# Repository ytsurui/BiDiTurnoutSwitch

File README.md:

# BiDi Turnout Switch

NMRA DCC 規格のうち、BiDi (RailCom) によって送信される車両のアドレス情報を利用して、接続されているポイント線路を自動的に転換することが可能な装置です。

本リポジトリには、基板設計データとファームウェアが含まれます。

## 開発環境

- KiCad Version (5.1.12)-1
- Microchip Studio Version 7.0.2542

## 各種ドキュメント

  * [パーツリスト](docs/partslist.md)

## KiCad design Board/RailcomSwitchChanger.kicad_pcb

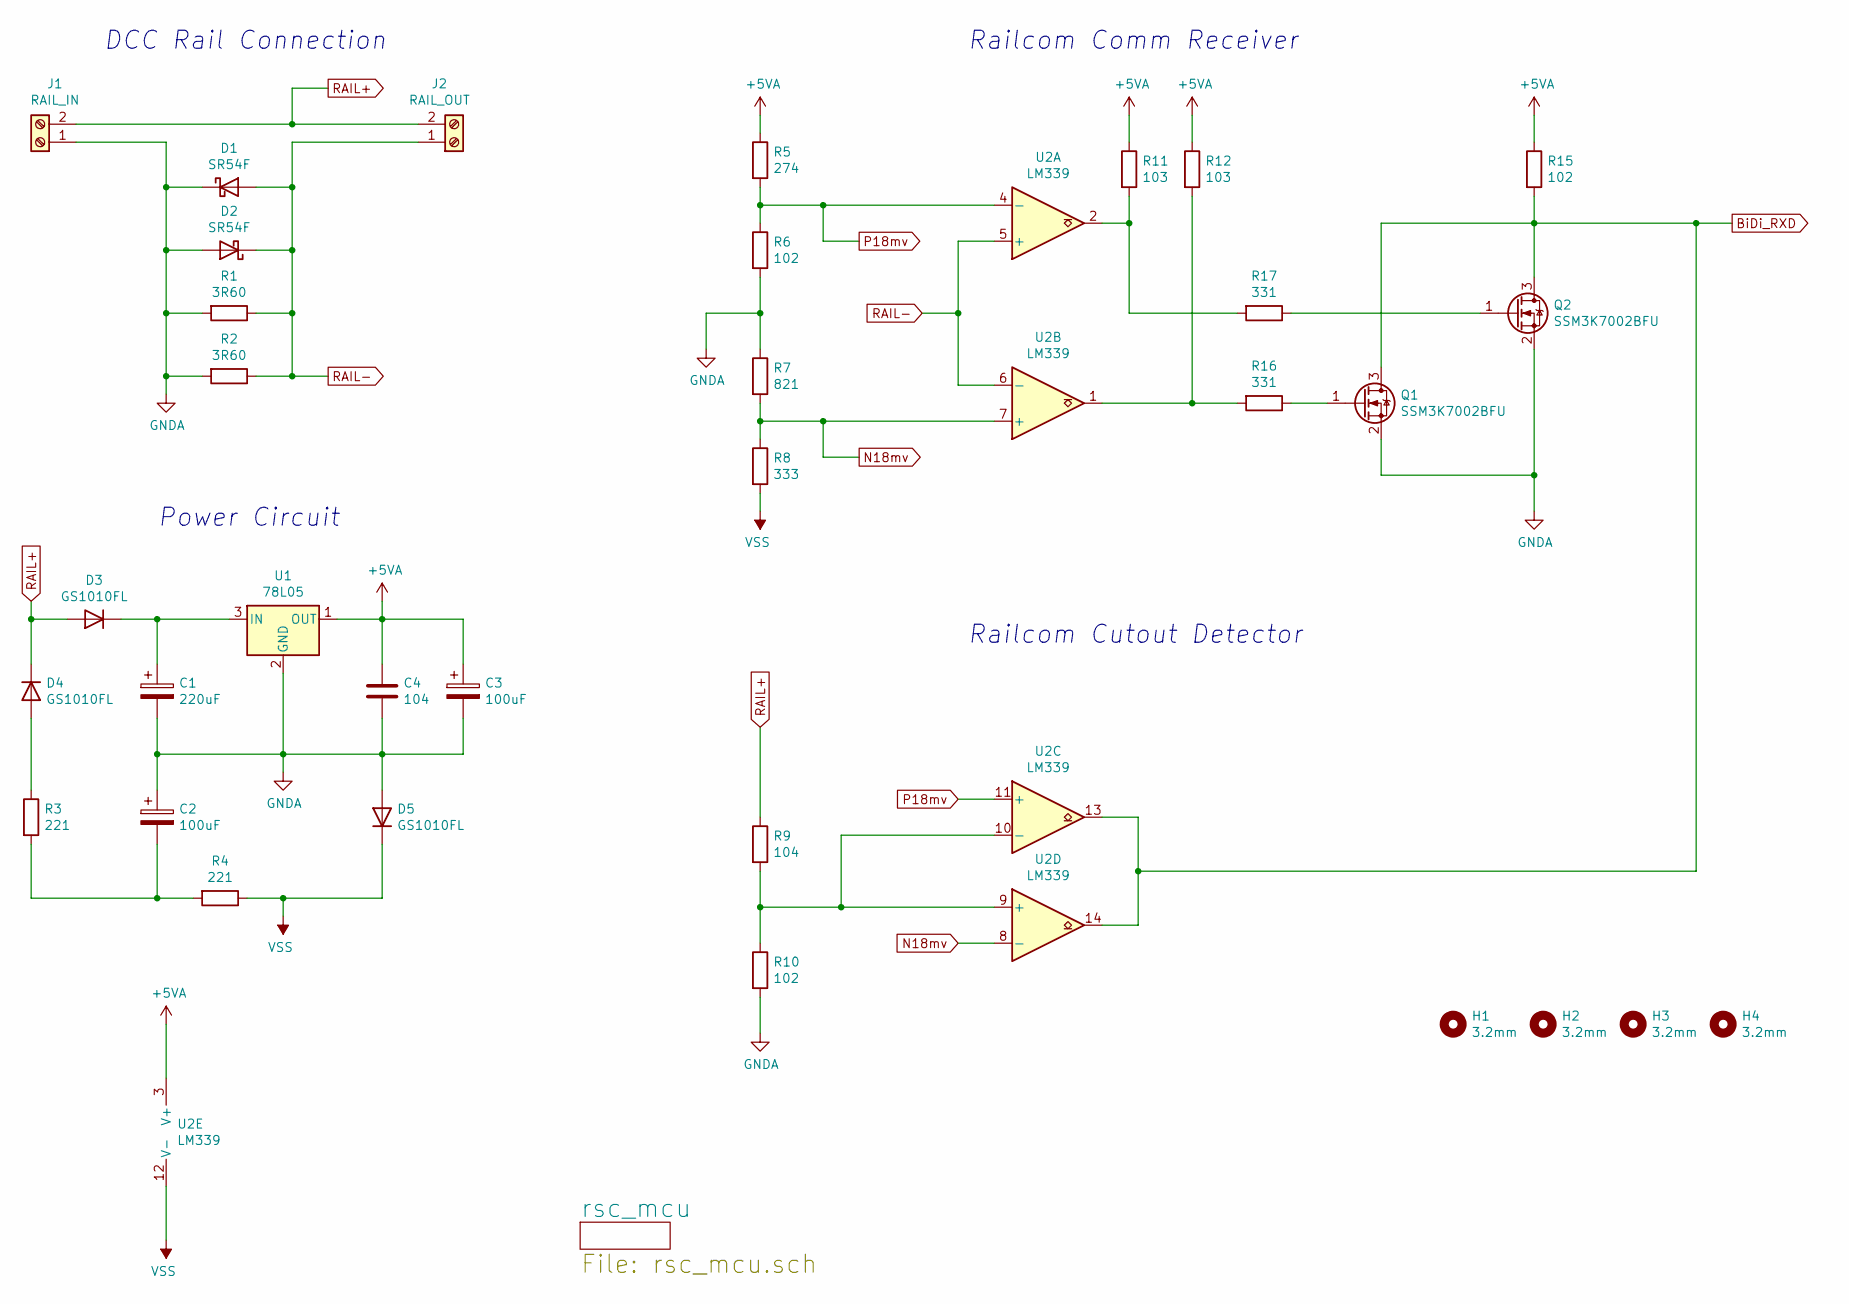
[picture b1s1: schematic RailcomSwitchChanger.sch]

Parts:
C1: 220uF; CAP_TH_6.3x11
C2, C3: 100uF; CAP_TH_5x11
C4: 104; C_1005
D1, D2: SR54F; SMBF
D3, D4, D5: GS1010FL; SOD-123FL
H1, H2, H3, H4: 3.2mm; HOLE_3.2mm
J1: RAIL_IN; TB111-2
J2: RAIL_OUT; TB111-2
Q1, Q2: SSM3K7002BFU; SC-70
R1, R2: 3R60; R_3225
R3, R4: 221; R_1608
R5: 274; R_1608
R6, R10, R15: 102; R_1608
R7: 821; R_1608
R8: 333; R_1608
R9: 104; R_1608
R11, R12: 103; R_1608
R16, R17: 331; R_1608
U1: 78L05; SOT-89-3
U2: LM339; SOIC-14

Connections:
+5VA: C3.1, C4.1, R5.1, R11.1, R12.1, R15.1, U1.1 (OUT), U2.3 (V+)
BiDi_RXD: Q1.3 (D), Q2.3 (D), R15.2, U2.13, U2.14; also elsewhere on the board
GNDA: C1.2, C2.1, C3.2, C4.2, D1.1 (K), D2.2 (A), D5.2 (A), J1.1, Q1.2 (S), Q2.2 (S), R1.2, R2.2, R6.2, R7.1, R10.2, U1.2 (GND); also elsewhere on the board
N18mv: R7.2, R8.1, U2.7 (+), U2.8 (-)
unnamed: C1.1, D3.1 (K), U1.3 (IN)
unnamed: C2.2, R3.2, R4.2
unnamed: D4.2 (A), R3.1
unnamed: Q1.1 (G), R16.1
unnamed: Q2.1 (G), R17.1
unnamed: R9.2, R10.1, U2.9 (+), U2.10 (-)
unnamed: R11.2, R17.2, U2.2
unnamed: R12.2, R16.2, U2.1
P18mv: R5.2, R6.1, U2.4 (-), U2.11 (+)
RAIL+: D3.2 (A), D4.1 (K), J1.2, J2.2, R9.1; also elsewhere on the board
RAIL-: D1.2 (A), D2.1 (K), J2.1, R1.1, R2.1, U2.5 (+), U2.6 (-)
VSS: D5.1 (K), R4.1, R8.2, U2.12 (V-)

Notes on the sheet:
Railcom Cutout Detector
Power Circuit
DCC Rail Connection
Railcom Comm Receiver

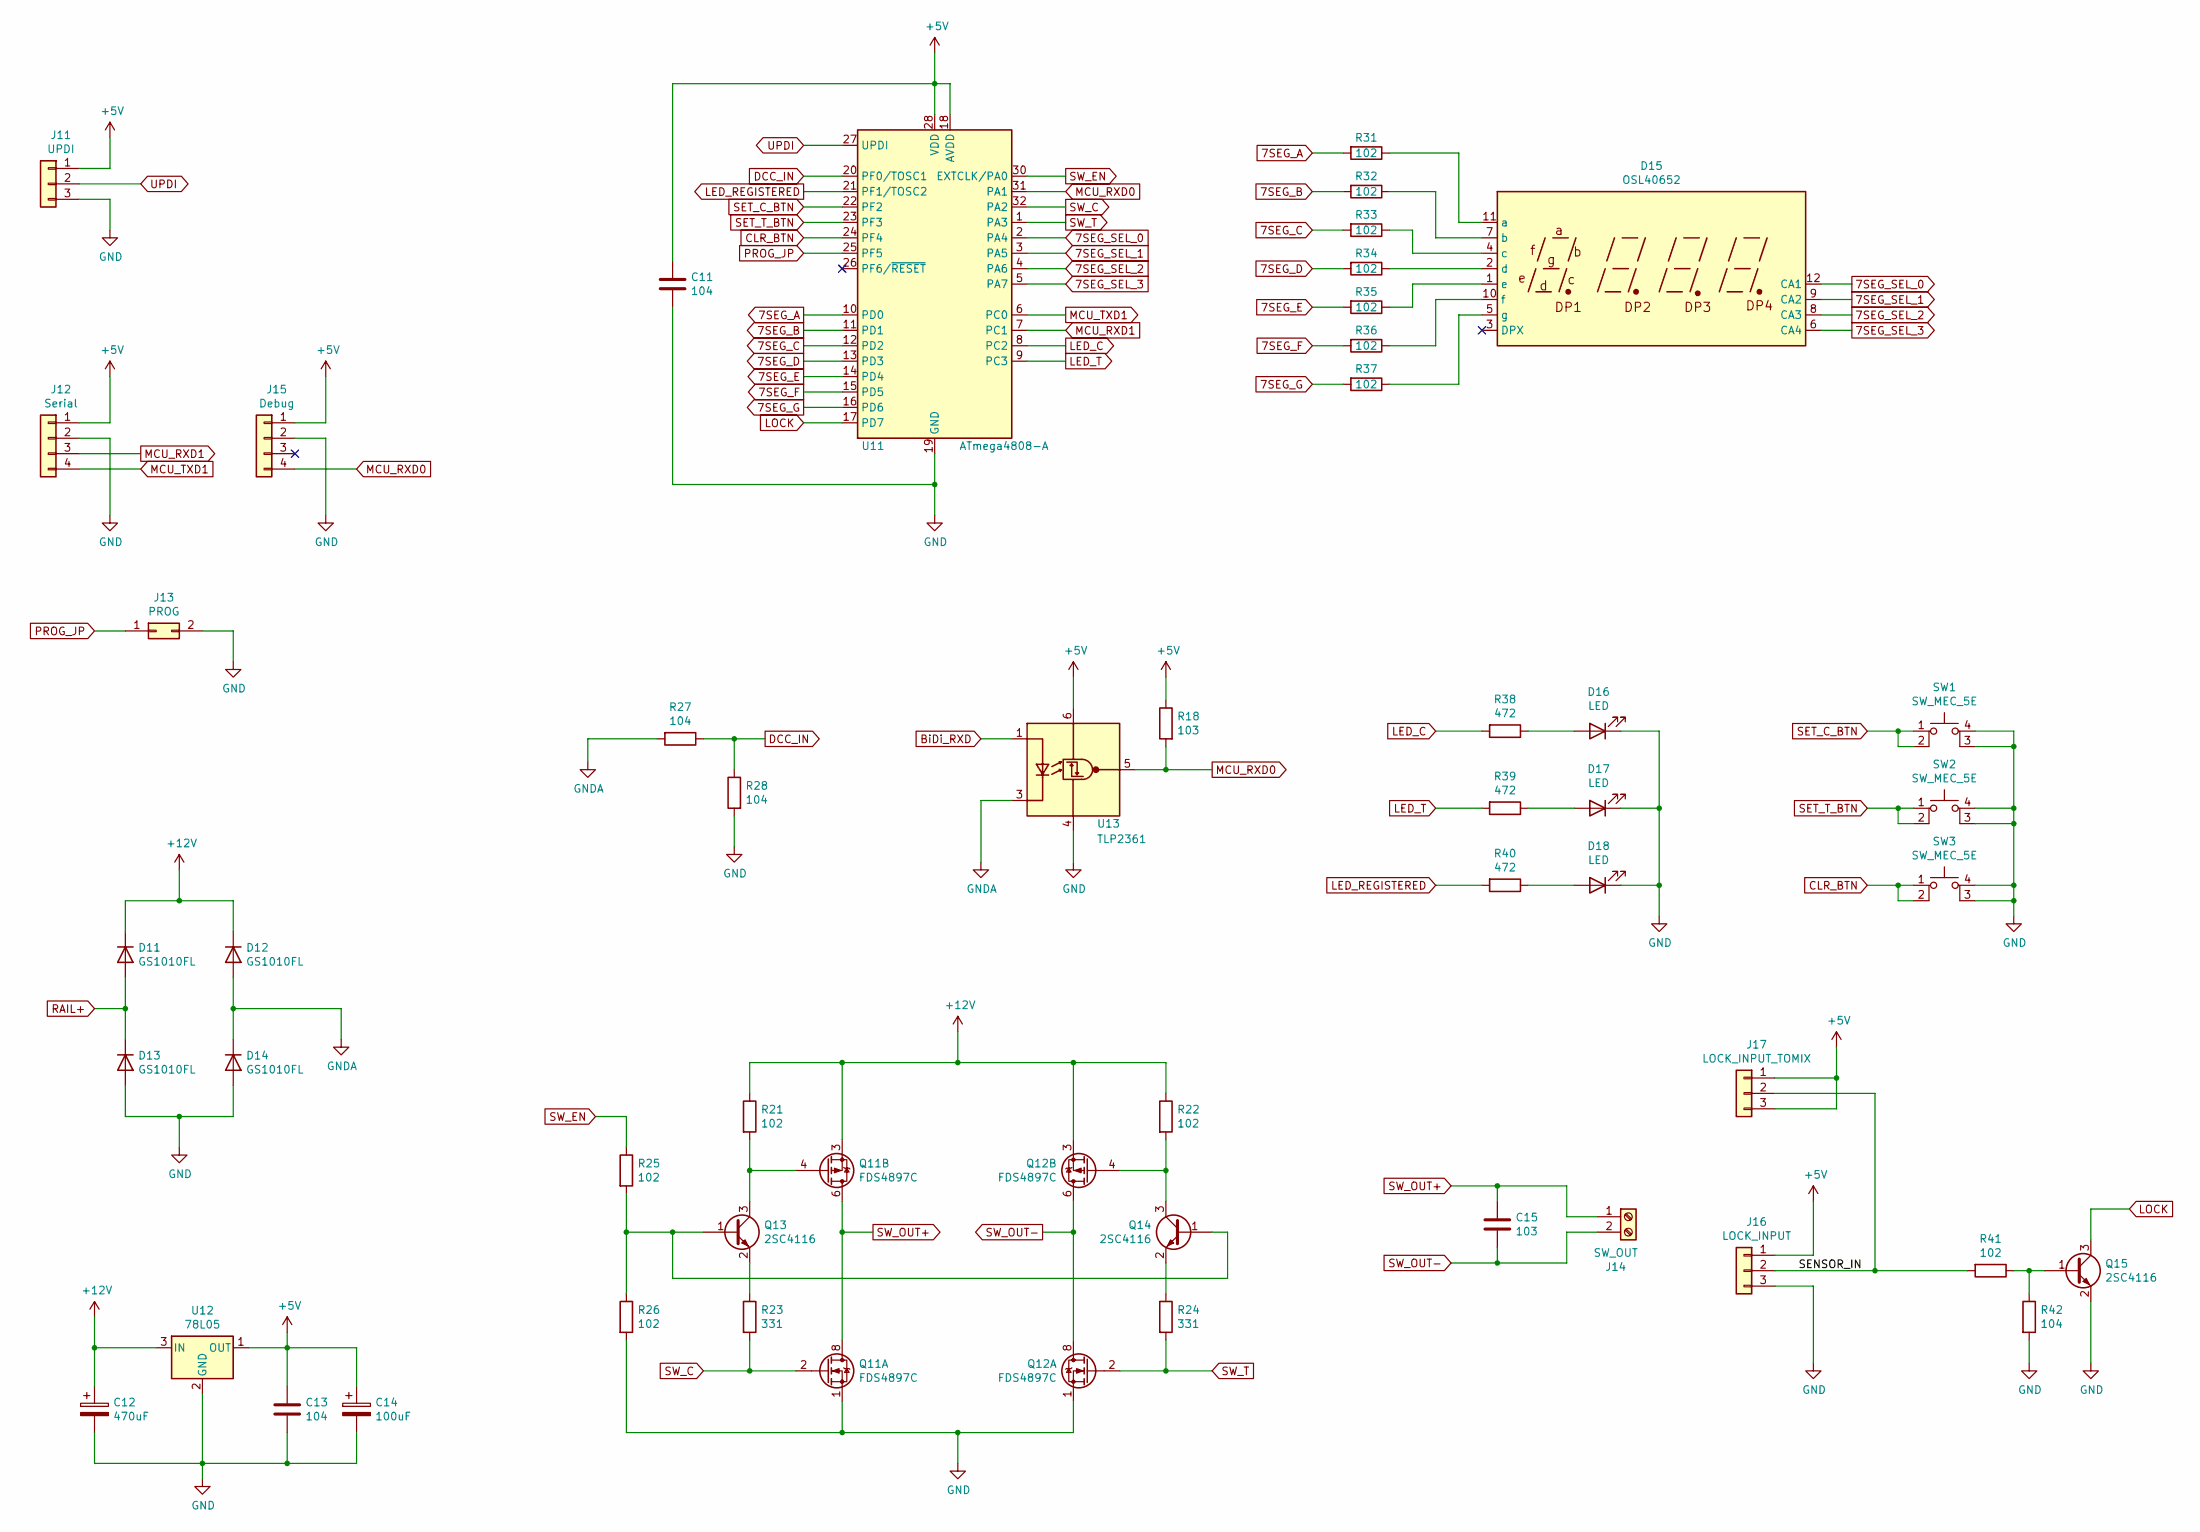
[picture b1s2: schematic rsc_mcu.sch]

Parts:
C11, C13: 104; C_1005
C12: 470uF; CAP_TH_8x11_5
C14: 100uF; CAP_TH_5x11
C15: 103; C_1005
D11, D12, D13, D14: GS1010FL; SOD-123FL
D15: OSL40652; OSL40562
D16, D17, D18: LED; LED_1608
J11: UPDI; PinHeader_01x03
J12: Serial; pin_array_1x4
J13: PROG; pin_array_1x2
J14: SW_OUT; TB111-2
J15: Debug; pin_array_1x4
J16: LOCK_INPUT; PinHeader_01x03
J17: LOCK_INPUT_TOMIX; Molex_0530480350
Q11, Q12: FDS4897C; SO-8
Q13, Q14, Q15: 2SC4116; SC-70
R18: 103; R_1608
R21, R22, R25, R26, R31, R32, R33, R34, R35, R36, R37, R41: 102; R_1608
R23, R24: 331; R_1608
R27, R28, R42: 104; R_1608
R38, R39, R40: 472; R_1608
SW1, SW2, SW3: SW_MEC_5E; TS-0606
U11: ATmega4808-A; TQFP-32_7x7mm_P0.8mm
U12: 78L05; SOT-89-3
U13: TLP2361; SO-6_5pin

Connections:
7SEG_A: R31.2, U11.10 (PD0)
7SEG_B: R32.2, U11.11 (PD1)
7SEG_C: R33.2, U11.12 (PD2)
7SEG_D: R34.2, U11.13 (PD3)
7SEG_E: R35.2, U11.14 (PD4)
7SEG_F: R36.2, U11.15 (PD5)
7SEG_G: R37.2, U11.16 (PD6)
7SEG_SEL_0: D15.12 (CA1), U11.2 (PA4)
7SEG_SEL_1: D15.9 (CA2), U11.3 (PA5)
7SEG_SEL_2: D15.8 (CA3), U11.4 (PA6)
7SEG_SEL_3: D15.6 (CA4), U11.5 (PA7)
+5V: C11.1, C13.1, C14.1, J11.1, J12.1, J15.1, J16.1, J17.1, J17.3, R18.1, U11.18 (AVDD), U11.28 (VDD), U12.1 (OUT), U13.6 (VDD)
+12V: C12.1, D11.1 (K), D12.1 (K), Q11.3 (1), Q12.3 (1), R21.1, R22.1, U12.3 (IN)
/rsc_mcu/SENSOR_IN: J16.2, J17.2, R41.2
BiDi_RXD: U13.1 (A); also elsewhere on the board
CLR_BTN: SW3.1, SW3.2, U11.24 (PF4)
DCC_IN: R27.1, R28.1, U11.20 (PF0/TOSC1)
GND: C11.2, C12.2, C13.2, C14.2, D13.2 (A), D14.2 (A), D16.1 (K), D17.1 (K), D18.1 (K), J11.3, J12.2, J13.2, J15.2, J16.3, Q11.1 (S), Q12.1 (S), Q15.2 (E), R26.2, R28.2, R42.2, SW1.3 (K), SW1.4 (A), SW2.3 (K), SW2.4 (A), SW3.3 (K), SW3.4 (A), U11.19 (GND), U11.29 (GND), U12.2 (GND), U13.4 (GND)
GNDA: D12.2 (A), D14.1 (K), R27.2, U13.3 (K); also elsewhere on the board
LED_C: R38.2, U11.8 (PC2)
LED_REGISTERED: R40.2, U11.21 (PF1/TOSC2)
LED_T: R39.2, U11.9 (PC3)
LOCK: Q15.3 (C), U11.17 (PD7)
MCU_RXD0: J15.4, R18.2, U11.31 (PA1), U13.5 (VO)
MCU_RXD1: J12.3, U11.7 (PC1)
MCU_TXD1: J12.4, U11.6 (PC0)
unnamed: D15.1 (e), R35.1
unnamed: D15.2 (d), R34.1
unnamed: D15.4 (c), R33.1
unnamed: D15.5 (g), R37.1
unnamed: D15.7 (b), R32.1
unnamed: D15.10 (f), R36.1
unnamed: D15.11 (a), R31.1
unnamed: D16.2 (A), R38.1
unnamed: D17.2 (A), R39.1
unnamed: D18.2 (A), R40.1
unnamed: Q11.4 (G), Q13.3 (C), R21.2
unnamed: Q12.4 (G), Q14.3 (C), R22.2
unnamed: Q13.1 (B), Q14.1 (B), R25.2, R26.1
unnamed: Q13.2 (E), R23.1
unnamed: Q14.2 (E), R24.1
unnamed: Q15.1 (B), R41.1, R42.1
PROG_JP: J13.1, U11.25 (PF5)
RAIL+: D11.2 (A), D13.1 (K); also elsewhere on the board
SET_C_BTN: SW1.1, SW1.2, U11.22 (PF2)
SET_T_BTN: SW2.1, SW2.2, U11.23 (PF3)
SW_C: Q11.2 (G), R23.2, U11.32 (PA2)
SW_EN: R25.1, U11.30 (EXTCLK/PA0)
SW_OUT+: C15.1, J14.1, Q11.5 (D), Q11.6 (D), Q11.7 (D), Q11.8 (D)
SW_OUT-: C15.2, J14.2, Q12.5 (D), Q12.6 (D), Q12.7 (D), Q12.8 (D)
SW_T: Q12.2 (G), R24.2, U11.1 (PA3)
UPDI: J11.2, U11.27 (UPDI)

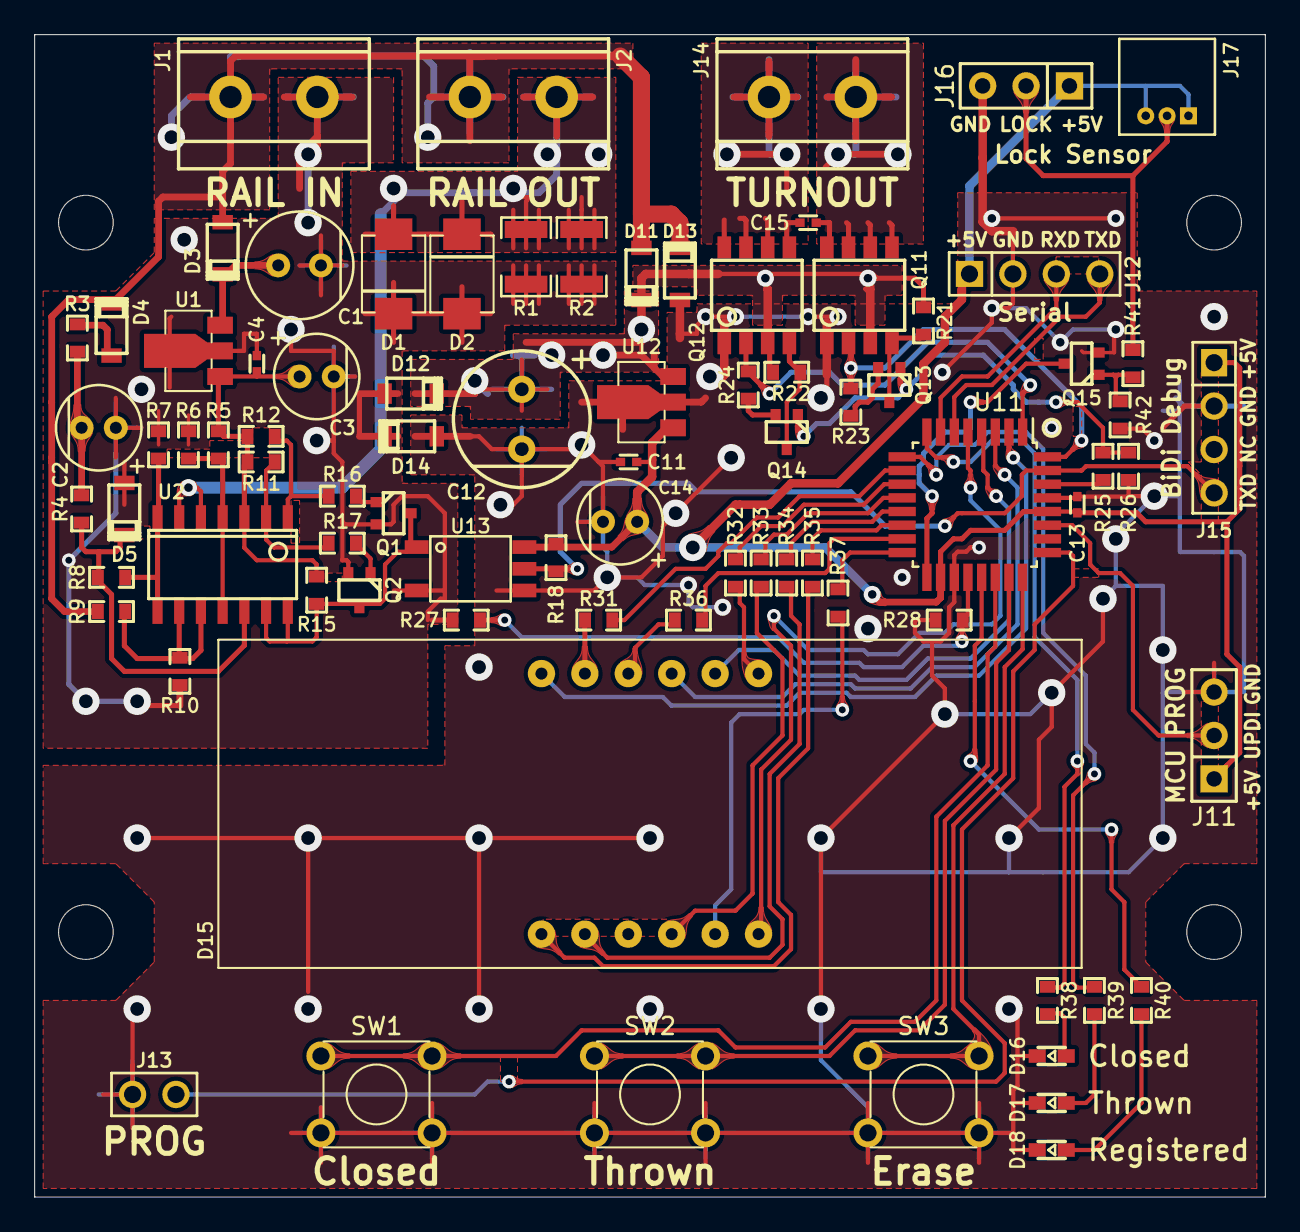
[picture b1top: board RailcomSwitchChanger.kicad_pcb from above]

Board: 2 copper layers, 72.0 x 68.0 mm, 86 parts (0 on the bottom side), 65 nets.

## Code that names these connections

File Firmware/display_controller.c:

/*
 * display_controller.c
 *
 * Created: 2021/12/31 0:49:56
 *  Author: Y.Tsurui
 */ 

#include <avr/io.h>
#include <avr/interrupt.h>
#include <avr/pgmspace.h>

#include "display_controller.h"

#define LED_A 0x01
#define LED_B 0x02
#define LED_C 0x04
#define LED_D 0x08
#define LED_E 0x10
#define LED_F 0x20
#define LED_G 0x40

uint8_t data_cache[4];
uint8_t select_flag = 0;

uint8_t power_flag = 0;

uint8_t appTimerFlag = 0;

//7-seg LED Port Assign
/*
A: PD0
B: PD1
C: PD2
D: PD3
E: PD4
F: PD5
G: PD6

CA1: PA4
CA2: PA5
CA3: PA6
CA4: PA7
*/

void set_port(uint8_t dec);

/*
ISR(TIMER1_COMPA_vect)
{
	appTimerFlag = 1;
	
	PORTD &= 0b11000011;
	
	if (power_flag) {
		PORTB &= 0x80;
		return;
	} else {
		set_port(data_cache[select_flag]);
		select_flag++;
	}	
	
	if (select_flag == 1) {
		PORTD |= 0b00000100;
	} else if (select_flag == 2) {
		PORTD |= 0b00010000;
	} else if (select_flag == 3) {
		PORTD |= 0b00100000;
	} else {
		PORTD |= 0b00001000;
		select_flag = 0;
	}
}

void set_7seg_timer(void)
{
	TCCR1A = 0b00000000;
	TCCR1B = 0b00001011;
	OCR1A = 128;
	OCR1B = OCR1A / 2;
	
	TIMSK |= 0b01000000;
	
	sei();
}
*/

void initDisplay(void) {
	PORTA.DIR |= 0xF0;
	PORTD.DIR |= 0x7F;
}

void displayClock(void) {
	PORTA.OUTCLR = 0xF0;
	
	if (power_flag) {
		PORTD.OUTCLR = 0x7F;
		return;
	} else {
		set_port(data_cache[select_flag]);
		select_flag++;
	}
	
	if (select_flag == 1) {
		PORTA.OUTSET = 0x80;
	} else if (select_flag == 2) {
		PORTA.OUTSET = 0x40;
	} else if (select_flag == 3) {
		PORTA.OUTSET = 0x20;
	} else {
		PORTA.OUTSET = 0x10;
		select_flag = 0;
	}
	
}

const PROGMEM uint8_t led7segDataTable[17] = {
	~(LED_A | LED_B | LED_C | LED_D | LED_E | LED_F),			// 0
	~(LED_B | LED_C),											// 1
	~(LED_A | LED_B | LED_D | LED_E | LED_G),					// 2
	~(LED_A | LED_B | LED_C | LED_D | LED_G),					// 3
	~(LED_B | LED_C | LED_F | LED_G),							// 4
	~(LED_A | LED_C | LED_D | LED_F | LED_G),					// 5
	~(LED_A | LED_C | LED_D | LED_E | LED_F | LED_G),			// 6
	~(LED_A | LED_B | LED_C),									// 7
	~(LED_A | LED_B | LED_C | LED_D | LED_E | LED_F | LED_G),	// 8
	~(LED_A | LED_B | LED_C | LED_D | LED_F | LED_G),			// 9
	~(LED_A | LED_B | LED_E | LED_F | LED_G),					// P
	~(LED_E | LED_G),											// r
	~(LED_C | LED_D | LED_E | LED_G),							// o
	~(LED_A | LED_B | LED_C | LED_D | LED_F | LED_G),			// g
	~(LED_G),													// -
	~(LED_G | LED_D | LED_E),									// C
	~(LED_E | LED_F | LED_D)									// L
};


void set_port(uint8_t dec)
{
	uint8_t readCache;
		
	//PORTB |= 0b01111111;
	PORTD.OUTSET = 0x7F;
	
	if (dec == 0xFF) {
		return;
	}
	
	if (dec > 0x80) {
		dec -= 119;
		readCache = pgm_read_byte(&led7segDataTable[dec]);
		//PORTB &= readCache;
		PORTD.OUT &= readCache;
	}
	
	if (dec < 10) {
		readCache = pgm_read_byte(&led7segDataTable[dec]);
		//PORTB &= readCache;
		PORTD.OUT &= readCache;
	}
	
	/*
	if (dec == 0) {
		//A-B-C-D-E-F
		PORTB &= ~(LED_A | LED_B | LED_C | LED_D | LED_E | LED_F);
	} else if (dec == 1) {	
		//B-C
		PORTB &= ~(LED_B | LED_C);
	} else if (dec == 2) {	
		//A-B-D-E-G
		PORTB &= ~(LED_A | LED_B | LED_D | LED_E | LED_G);
	} else if (dec == 3) {	
		//A-B-C-D-G
		PORTB &= ~(LED_A | LED_B | LED_C | LED_D | LED_G);
	} else if (dec == 4) {	
		//B-C-F-G
		PORTB &= ~(LED_B | LED_C | LED_F | LED_G);
	} else if (dec == 5) {	
		//A-C-D-F-G
		PORTB &= ~(LED_A | LED_C | LED_D | LED_F | LED_G);
	} else if (dec == 6) {	
		//A-C-D-E-F-G
		PORTB &= ~(LED_A | LED_C | LED_D | LED_E | LED_F | LED_G);
	} else if (dec == 7) {	
		//A-B-C
		PORTB &= ~(LED_A | LED_B | LED_C);
	} else if (dec == 8) {	
		//A-B-C-D-E-F-G
		PORTB &= ~(LED_A | LED_B | LED_C | LED_D | LED_E | LED_F | LED_G);
	} else if (dec == 9) {	
		//A-B-C-D-F-G
		PORTB &= ~(LED_A | LED_B | LED_C | LED_D | LED_F | LED_G);
	} else if (dec == 0x81) {
		//P (A-B-E-F-G)
		PORTB &= ~(LED_A | LED_B | LED_E | LED_F | LED_G);
	} else if (dec == 0x82) {
		//R (A-E-F)
		PORTB &= ~(LED_A | LED_E | LED_F);
	} else if (dec == 0x83) {
		//O (A-B-C-D-E-F)
		PORTB &= ~(LED_A| LED_B | LED_C | LED_D | LED_E | LED_F);
	} else if (dec == 0x84) {
		//G (A-B-C-D-F-G)
		PORTB &= ~(LED_A | LED_B | LED_C | LED_D | LED_F | LED_G);
	}
	*/
	
}

void set_7seg_data(uint16_t data)
{
	uint8_t i;
	
	for (i = 0; i < 4; i++) {
		if ((data == 0) && (i != 0)) {
			data_cache[i] = 0xFF;
		} else {
			data_cache[i] = data % 10;
			data = data / 10;
		}
	}
}

void set_led_power_stat(uint8_t stat)
{
	power_flag = stat;
}

void set_prog_mode(void)
{
	data_cache[0] = 0x84;
	data_cache[1] = 0x83;
	data_cache[2] = 0x82;
	data_cache[3] = 0x81;
}

void set_clr_msg(void)
{
	data_cache[0] = 0x82;
	data_cache[1] = 0x87;
	data_cache[2] = 0x86;
	data_cache[3] = 0xFF;
}

void set_null_msg(uint8_t pos) {
	uint8_t i;
	
	for (i = 0; i < 4; i++) {
		if (i == pos) {
			data_cache[i] = 0x85;
		} else {
			data_cache[i] = 0xFF;
		}
	}
}

uint8_t appTimer(void) {
	if (appTimerFlag) {
		appTimerFlag = 0;
		return (1);
	}
	return (0);
}

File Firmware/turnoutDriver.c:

/*
 * turnoutDriver.c
 *
 * Created: 2021/12/31 15:43:38
 *  Author: Y.Tsurui
 */

#include <avr/io.h>
#include "turnoutDriver.h"

uint8_t turnoutMoveStartFlag;
uint16_t turnoutCounter;
uint8_t turnoutMove;
uint8_t turnoutNowStat;

uint16_t turnoutLockCounter = 0;
#define TURNOUT_LOCK_MAX 3000;

uint8_t turnoutLockLEDcounter = 0;


void turnoutClock(void) {
	if (turnoutLockCounter > 0) {
		turnoutLockCounter--;
			
		
		if (turnoutLockCounter == 0) {
			if (turnoutNowStat == TURNOUT_CLOSE) {
				// LED Closed On
				PORTC.OUTSET = 0x04;
			} else if (turnoutNowStat == TURNOUT_THROWN) {
				// LED Thrown On
				PORTC.OUTSET = 0x08;
			}
			turnoutLockLEDcounter = 0;
		} else {
			turnoutLockLEDcounter++;
			if (turnoutLockLEDcounter == 0x3F) {
				if (turnoutNowStat == TURNOUT_CLOSE) {
					PORTC.OUTTGL = 0x04;
				} else if (turnoutNowStat == TURNOUT_THROWN) {
					PORTC.OUTTGL = 0x08;
				}
				turnoutLockLEDcounter = 0;
			}
		}
	}
	
	if (turnoutCounter == 0) {
		if (turnoutMoveStartFlag == 0) {
			return;
		}
		
		if (turnoutLockCounter != 0) {
			return;
		} 
		
		turnoutMove = turnoutMoveStartFlag;
		turnoutNowStat = turnoutMoveStartFlag;
		turnoutMoveStartFlag = 0;
		turnoutCounter = 1;
	}
	
	if (turnoutCounter == 1) {
		
		if (turnoutMove == TURNOUT_CLOSE) {
			PORTC.OUTSET = 0x04;
			PORTC.OUTCLR = 0x08;
		} else if (turnoutMove == TURNOUT_THROWN) {
			PORTC.OUTSET = 0x08;
			PORTC.OUTCLR = 0x04;
		} else {
			turnoutCounter = 0;
			turnoutMove = 0;
			return;
		}
	} else if (turnoutCounter < 1000) {
		if ((turnoutCounter & 0x007F) == 0x007F) {
			if (turnoutMove == TURNOUT_CLOSE) {
				PORTC.OUTTGL = 0x04;
				PORTC.OUTCLR = 0x08;
			} else if (turnoutMove == TURNOUT_THROWN) {
				PORTC.OUTTGL = 0x08;
				PORTC.OUTCLR = 0x04;
			}
		}
	} else if (turnoutCounter == 1001) {
		if (turnoutMove == TURNOUT_CLOSE) {
			PORTA.OUTSET = 0x05;
			PORTC.OUTSET = 0x04;
			PORTC.OUTCLR = 0x08;
		} else if (turnoutMove == TURNOUT_THROWN) {
			PORTA.OUTSET = 0x09;
			PORTC.OUTSET = 0x08;
			PORTC.OUTCLR = 0x04;
		} else {
			turnoutCounter = 0;
			turnoutMove = 0;
			return;
		}
		turnoutMove = 0;
	} else if (turnoutCounter == 1250) {
		PORTA.OUTCLR = 0x0D;
	} else if (turnoutCounter >= 2000) {
		if (turnoutMove > 0) {
			turnoutCounter = 1;
			return;
		}
		turnoutCounter = 0;
		return;
	}
	
	turnoutCounter++;
}

void initTurnoutDriver(void) {
	PORTA.DIRSET = 0x0D;	// output PA0,PA2,PA3
	PORTC.DIRSET = 0x0C;	// output PC2,PC3 (LED)
	turnoutCounter = 0;
}

void setTurnout(uint8_t dir) {
	//turnoutMove = dir;
	//if (turnoutCounter == 0) {
		//turnoutCounter = 1;
		//turnoutMoveStartFlag = 1;
	//}
	//turnoutMoveStartFlag = 1;
	turnoutMoveStartFlag = dir;
}

void resetTurnoutTimer(void) {
	turnoutLockCounter = TURNOUT_LOCK_MAX;
}

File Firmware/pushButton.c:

/*
 * pushButton.c
 *
 * Created: 2021/12/31 14:48:37
 *  Author: Y.Tsurui
 */ 

#include <avr/io.h>
#define BUTTON_COUNT_THRESHOLD 10
#define BUTTON_COUNT_MAX 20

uint8_t btnCount[4];

uint8_t buttonLastStat;
uint8_t buttonChangeFlag;


void buttonClock() {
	uint8_t i;
	uint8_t buttonStat;
	uint8_t buttonMask;
	
	buttonStat = (PORTF.IN & 0x3C) >> 2;
	buttonMask = 0x01;
	
	for (i = 0; i < 4; i++) {
		if (buttonStat & buttonMask) {
			if (btnCount[i] > 0) {
				btnCount[i]--;
			}
		} else {
			if (btnCount[i] < BUTTON_COUNT_MAX) {
				btnCount[i]++;
			}
		}
		
		if (btnCount[i] > BUTTON_COUNT_THRESHOLD) {
			if (~buttonLastStat & buttonMask) {
				buttonLastStat |= buttonMask;
				buttonChangeFlag |= buttonMask;
			}
		} else {
			if (buttonLastStat & buttonMask) {
				buttonLastStat &= ~buttonMask;
				buttonChangeFlag |= buttonMask;
			}
		}
		
		buttonMask = buttonMask << 1;
	}
}

void initButton(void) {
	PORTF.DIRCLR = 0x3C;	//(PF2 / PF3 / PF4 / PF5)
	PORTF.PIN2CTRL = PORT_PULLUPEN_bm;	// C
	PORTF.PIN3CTRL = PORT_PULLUPEN_bm;	// T
	PORTF.PIN4CTRL = PORT_PULLUPEN_bm;	// CLR
	PORTF.PIN5CTRL = PORT_PULLUPEN_bm;	// PROG
}

uint8_t getButtonStat(uint8_t buttonId) {
	if (btnCount[buttonId] > BUTTON_COUNT_THRESHOLD) {
		return (1);	
	}
	return (0);
}

uint8_t pushButtonEvent(uint8_t buttonId) {
	uint8_t buttonMask;
	
	buttonMask = 0x01 << buttonId;
	
	if (buttonChangeFlag & buttonMask) {
		buttonChangeFlag &= ~buttonMask;
		return (1);
	}
	return (0);
}

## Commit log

2022-08-10 Add parts list
2022-08-10 Board Rev.2
